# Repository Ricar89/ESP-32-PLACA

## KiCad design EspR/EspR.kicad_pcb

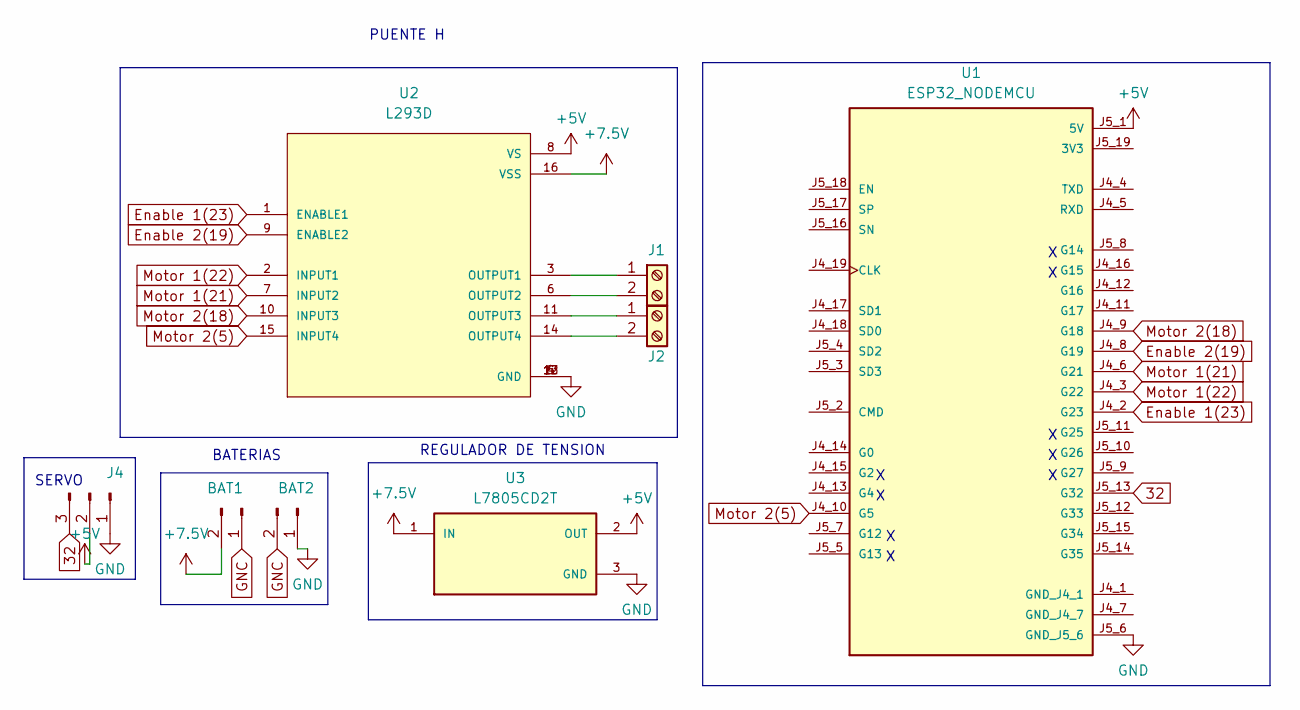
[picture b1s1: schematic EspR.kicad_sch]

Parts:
BAT1, BAT2: Conn_01x02_Pin; PinHeader_1x02_P2.54mm_Vertical
J1, J2: Screw_Terminal_01x02; BORNERA2_DUO
J4: Conn_01x03_Pin; PinHeader_1x03_P2.54mm_Vertical
U1: ESP32_NODEMCU; MODULE_ESP32_NODEMCU
U2: L293D; DIP880W50P254L2000H510Q16
U3: L7805CD2T; TO254P1542X460-3N; PARTREV 36

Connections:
32: J4.3, U1.J5_13 (G32)
+5V: J4.2, U1.J5_1 (5V), U2.8 (VS), U3.2 (OUT)
+7.5V: BAT1.2, U2.16 (VSS), U3.1 (IN)
Enable 1(23): U1.J4_2 (G23), U2.1 (ENABLE1)
Enable 2(19): U1.J4_8 (G19), U2.9 (ENABLE2)
GNC: BAT1.1, BAT2.2
GND: BAT2.1, J4.1, U1.J5_6 (GND_J5_6), U2.4 (GND), U2.5 (GND), U2.12 (GND), U2.13 (GND), U3.3 (GND)
Motor 1(21): U1.J4_6 (G21), U2.7 (INPUT2)
Motor 1(22): U1.J4_3 (G22), U2.2 (INPUT1)
Motor 2(5): U1.J4_10 (G5), U2.15 (INPUT4)
Motor 2(18): U1.J4_9 (G18), U2.10 (INPUT3)
unnamed: J1.1, U2.3 (OUTPUT1)
unnamed: J1.2, U2.6 (OUTPUT2)
unnamed: J2.1, U2.11 (OUTPUT3)
unnamed: J2.2, U2.14 (OUTPUT4)

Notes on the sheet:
SERVO
REGULADOR DE TENSION
PUENTE H
BATERIAS

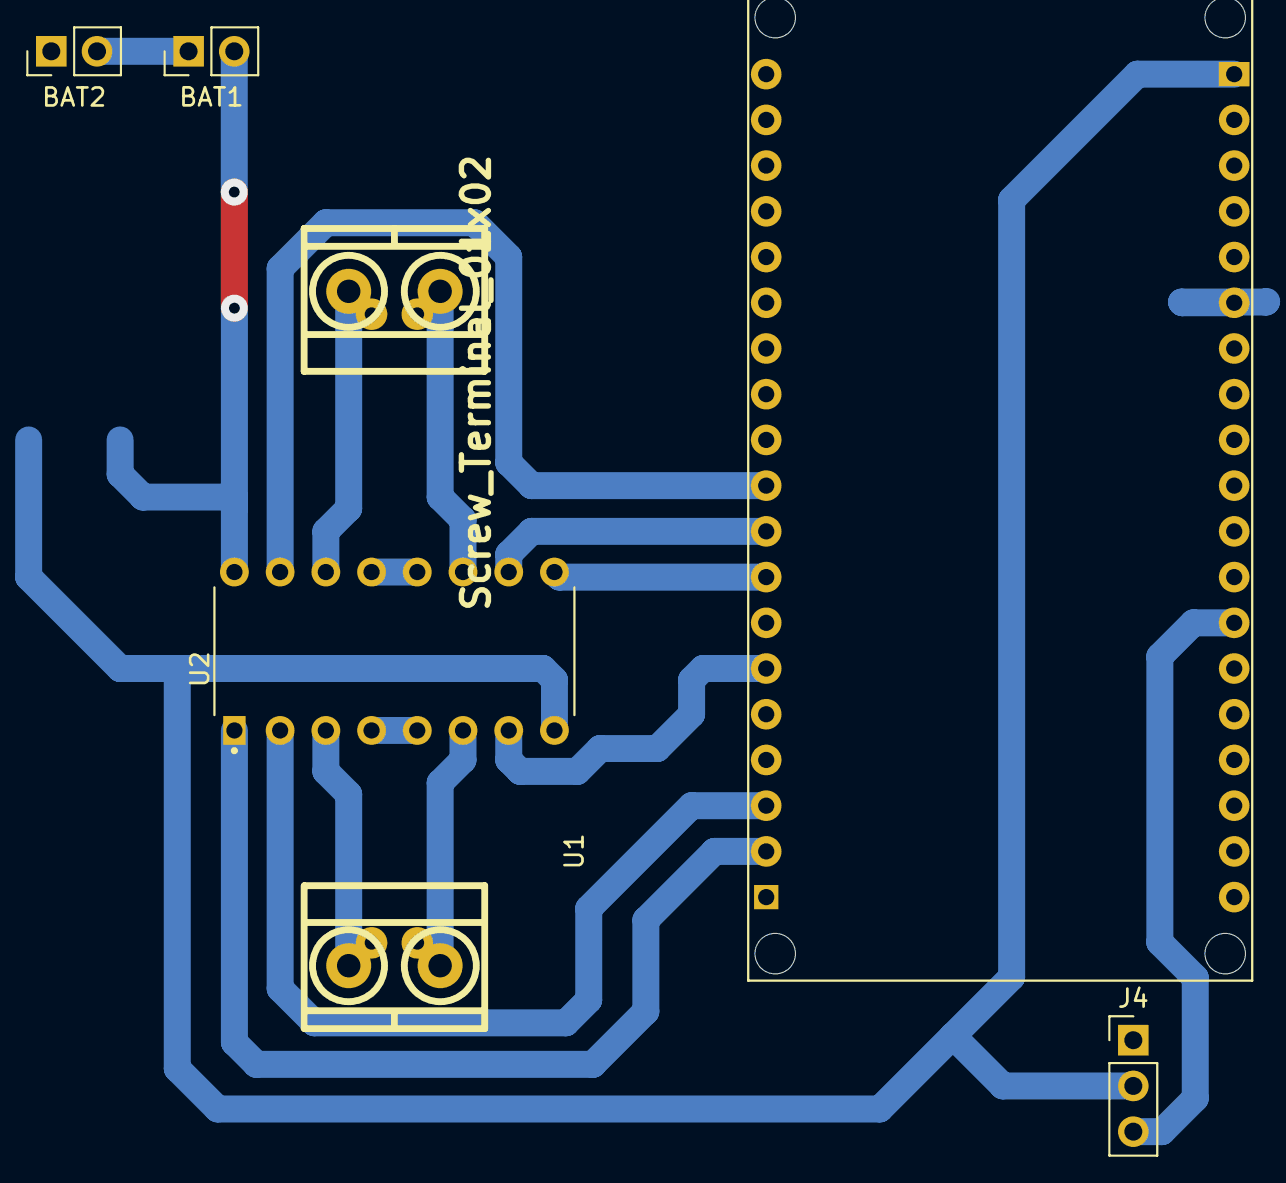
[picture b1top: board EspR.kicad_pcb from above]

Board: 2 copper layers, 8 parts (1 on the bottom side), 15 nets.
